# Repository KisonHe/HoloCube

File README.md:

## 安装lvgl字体与图片工具
```bash
npm i lv_font_conv 
npm i lv_img_conv
```
[Download](https://github.com/googlefonts/noto-cjk/raw/main/Sans/Mono/NotoSansMonoCJKsc-Regular.otf)

## OTA
参考 
1. https://docs.platformio.org/en/latest/platforms/espressif32.html#over-the-air-ota-update
2. https://github.com/platformio/bintray-secure-ota

2的这个repo基本就是想做的了（

有空了仔细看一下，看是否能用github actions自动化掉

我草，pio真牛逼，test也还没有看

## Wifi 
https://iotespresso.com/create-captive-portal-using-esp32/
Run `putHTML.py` to update the portal html code

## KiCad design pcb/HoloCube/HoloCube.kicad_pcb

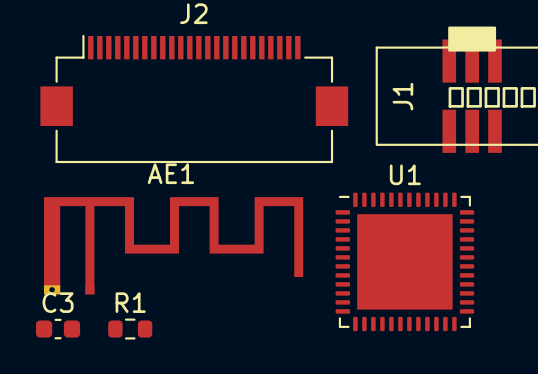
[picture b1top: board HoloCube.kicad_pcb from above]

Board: 2 copper layers, 6 parts (0 on the bottom side), 6 nets, no tracks yet.

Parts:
AE1: Antenna; Texas_SWRA117D_2.4GHz_Right
C3: 0.1uF; C_0603_1608Metric
J1: ESPProgUART_RX; IDC_1.27mm_6P
J2: Conn_01x24_Female; Hirose_FH12-24S-0.5SH_1x24-1MP_P0.50mm_Horizontal
R1: 10k; R_0603_1608Metric
U1: ESP32-PICO-D4; QFN-48-1EP_7x7mm_P0.5mm_EP5.3x5.3mm

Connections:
+3.3VA: U1.1 (VDDA), U1.3 (VDDA3P3), U1.4 (VDDA3P3), U1.19 (VDD3P3_RTC), U1.37 (VDD3P3_CPU), U1.43 (VDDA), U1.46 (VDDA)
/EN: C3.1, J1.1 (EN), R1.2, U1.9 (EN)
/RX: J1.5 (ESPRXD), U1.40 (U0RXD/IO3)
/TX: J1.3 (ESPTXD), U1.22 (IO2)
GND: C3.2, J1.4 (GND), U1.49 (GND)
unnamed: AE1.1 (A), U1.2 (LNA_IN)

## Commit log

2022-04-26 Init Commit
2022-04-26 Init Commit with only framework
2022-04-26 lvgl
2022-05-06 pio init
2022-05-06 Init
2022-05-06 Init with port_esp32
2022-05-06 Submodules
2022-05-06 Working Demo
2022-05-06 Restore PCB
2022-05-07 Change pcb to submodule
2022-05-07 Update PCB
2022-05-13 disp_buf seems not right
2022-05-13 Arduino Dev
2022-05-15 Simple Working Demo
2022-05-15 Finish PCB V0.1 test
2022-05-17 Chinese Demo
2022-05-17 Add font tool
2022-05-18 lvgl type test
2022-05-21 V0.2 pcb test
2022-05-21 Working Button Lib
2022-05-21 button as submodule
2022-05-22 Add somemore FrameWork
2022-05-23 More FramWork
2022-05-23 Simple Demo
2022-05-23 More framework
2022-05-26 Screen is dead
    Stop for now until back to shenzhen
2022-06-09 Show no app
2022-06-10 Improve stuff and found new bug
2022-06-13 Bug Fix
2022-06-13 Unfinished multi app test
2022-06-13 indrv warpper
2022-06-14 Stash
2022-06-14 App Switch demo&Bug Fix
2022-06-14 更新PCB&menuapp改进
2022-06-14 Why is image so slow?
2022-06-14 Sooooo slow
2022-06-14 Try to get DMA running
2022-06-14 Wondering with DMA
2022-06-14 Pain
2022-06-14 Fix dir bug
2022-06-14 Demo
2022-06-15 Example Tomato Timer label
2022-06-17 Improve Tomato
2022-06-21 Watch Test
2022-06-21 Separate
2022-06-24 ESP32 So Slow
2022-06-24 Update lib dep
2022-06-25 Update asserts & mainmenu
2022-06-25 Port to platform = espressif32>4.0
2022-06-26 Found a html on internet
2022-06-26 Fix zoom inelegantly
    Well I dont know how to write this css...
    Googled this violent zoom fixing...
2022-06-26 Successful Captive Portal
2022-06-26 Compelete html
2022-06-27 Well with spiffs it is even slower...
